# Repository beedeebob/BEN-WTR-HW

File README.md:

# BEN-WTR-HW
Hardware schematics for the BEN-WTR weather diy system

## DIY PCBs Used
- STM32 Blue Pill (Modified with a STM32f303CBT6)
- ESP-01
- W25Q SPI DIY PCB
- 3V3 DIY PCB
- BME280 SPI DIY PC

## Firmware
https://github.com/beedeebob/BEN-WTR-APP

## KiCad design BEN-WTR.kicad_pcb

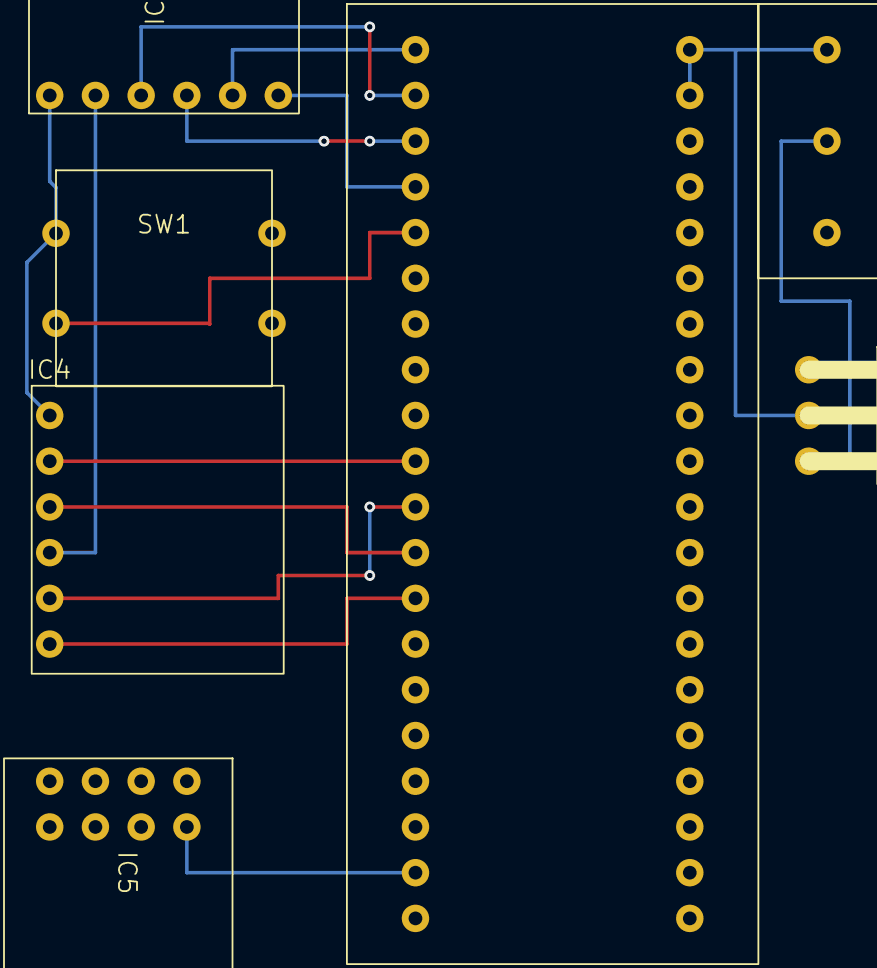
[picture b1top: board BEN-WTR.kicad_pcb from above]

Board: 2 copper layers, 7 parts (0 on the bottom side), 16 nets.

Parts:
IC1: BLUE PILL
IC2: REGULATOR
IC3: BME280-SPI
IC4: FLASH-SPI
IC5: ESP-01
J1: Screw_Terminal_01x03; TERMINAL-03
SW1: SW_Push; BIG BUTTON

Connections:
+3V3: IC1.20 (3.3), IC1.38 (3.3), IC2.1 (VO), IC3.1 (VCC), IC4.1 (VCC), IC5.7 (3V3), SW1.1
GND: IC1.19 (G), IC1.39 (G), IC1.40 (G), IC2.2 (GND), IC3.2 (GND), IC4.4 (GND), IC5.2 (GND), J1.1
unnamed: IC1.5 (A8), SW1.2
unnamed: IC1.10 (A15), IC4.2 (~CS)
unnamed: IC1.11 (B3), IC4.5 (CLK)
unnamed: IC1.12 (B4), IC4.3 (DO)
unnamed: IC1.13 (B5), IC4.6 (DI)
unnamed: IC1.14 (B6), IC5.8 (GPIO3-RX)
unnamed: IC1.15 (B7), IC5.1 (GPIO1-TX)
unnamed: IC1.16 (B8), IC5.3 (~CH_PD/EN)
unnamed: IC1.17 (B9), IC5.6 (GPIO0-FLASH)
unnamed: IC1.1 (B12), IC3.5 (CSB)
unnamed: IC1.2 (B13), IC3.3 (SCL)
unnamed: IC1.3 (B14), IC3.4 (SDA)
unnamed: IC1.4 (B15), IC3.6 (SDO)
unnamed: IC2.3 (Vin), J1.2

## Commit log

2025-03-15 Added the kicad layout
